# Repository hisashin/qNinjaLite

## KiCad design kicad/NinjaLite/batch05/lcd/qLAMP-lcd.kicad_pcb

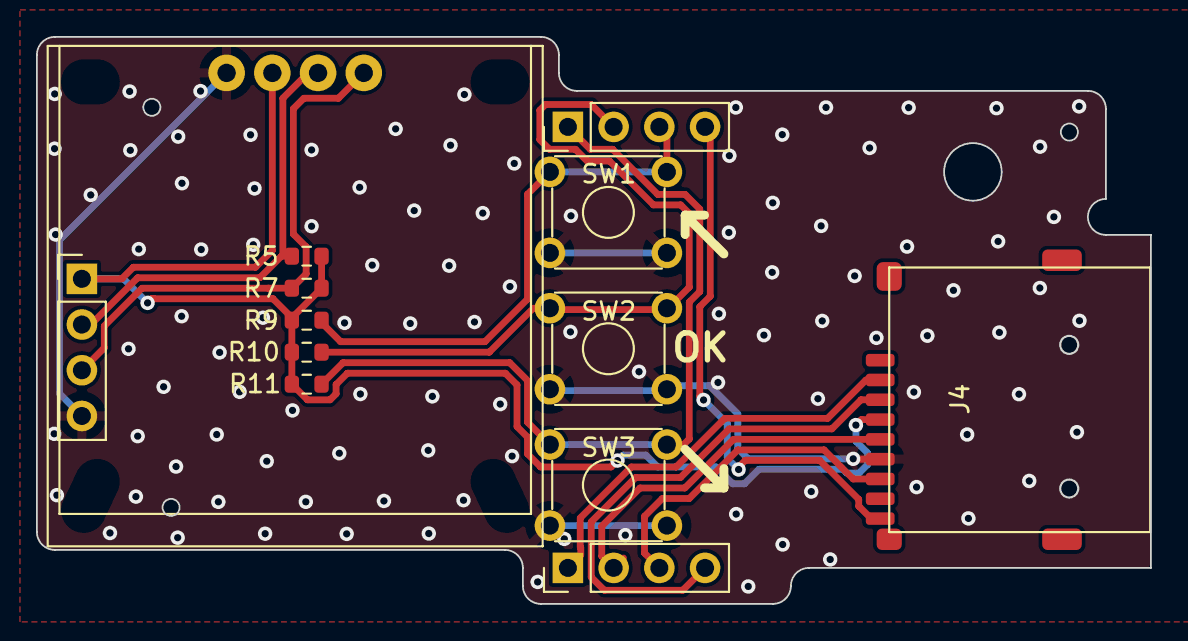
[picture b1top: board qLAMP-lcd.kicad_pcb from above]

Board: 2 copper layers, 61.9 x 31.5 mm, 13 parts (0 on the bottom side), 12 nets.

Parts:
D2: I2C_SSD1306_LCD; ALI_I2C_LCD
J1, J2, J3: Conn_01x04_Male; PinHeader_1x04_P2.54mm_Vertical
J4: ALI_Micro_SD_Card; ALI_microSD
R5, R7, R9, R10, R11: 100k; R_0603_1608Metric
SW1, SW2, SW3: TACTILE_4; SW_TH_Tactile_Omron_B3F-10xx

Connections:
3V3D: D2.2 (VCC), J3.1, J4.4 (VDD), R5.1, R7.1, R9.1, R10.1, R11.1
GND: D2.1 (GND), J3.4, J4.6 (VSS), SW1.3, SW1.4, SW2.3, SW2.4, SW3.3, SW3.4
I2C_SCL: D2.3 (SCL), J3.2, R5.2
I2C_SDA: D2.4 (SDA), J3.3, R7.2
MISO: J2.3, J4.7 (DAT0)
MOSI: J2.4, J4.3 (CMD)
SCLK: J2.2, J4.5 (CLK)
SD_CD: J1.4, J4.Cd (CD)
SD_CS: J2.1, J4.2 (DAT3/CD)
TACT1: J1.3, R9.2, SW1.1, SW1.2
TACT2: J1.2, R10.2, SW2.1, SW2.2
TACT3: J1.1, R11.2, SW3.1, SW3.2
